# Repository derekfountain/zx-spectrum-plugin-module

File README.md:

# ZX Spectrum Plugin Module

This is small interposer board I created for the ZX Spectrum's edge connector.

## Improved edge connector

The Spectrum's edge connector can be rather tight, and repeated
insertion and removal of an interface you're prototyping can wear it
away. The copper pads are difficult to repair if they wear too thin
and stop working. Also, the edge connector sockets need cutting to
size and a locating pin inserting, which is all a bit fiddly and so
they are relatively expensive.

The interposer board converts the Spectrum's edge connector hardware
format to a much more standard row of 2.54" header pins. It looks like
this:

Front:

Back:

So you solder a Spectrum edge connector to the front:

and a couple of rows of standard header sockets to the back:

The board you're prototyping can then use standard header pins
in place the normal Spectrum edge connector socket:

This allows you to plug the prototype into the interposer, as opposed
to the Spectrum's edge connector:

So now the prototype can be put onto, and pulled off, the Spectrum
without wearing the edge connector, and each prototype iteration costs
you 2 rows of standard header pins instead of an edge connector
socket.

## Another use

A rather unintended alternative use for the board is to expose the
edge connector pins more easily. It's a lot easier to insert a wire
into a header socket and connect the other end to the oscilloscope
probe than it is to try to get the probe on a certain Z80 pin, for
example.

To this end I ended up making a "breakout" version as well, which also
exposes the edge connector's signals on connection points. I'm not
sure this version is useful, since I think the prototype board and the
back of the Spectrum will foul access to the extra test points. I
didn't pursue it, but it might be useful to someone.

### Construction

Construction is trivial, but try to use long strip of sockets cut
down, as opposed to what I did which was use a strip of 20 butted up
against a strip of 8. It turns out the sides of the strips are
slightly thicker plastic then that between the connection points, so
when you butt them up together you get a wider gap between the
individual points at the joint. It's very slight, just a fraction of a
millimetre, but it makes fitting the header pins into the sockets a
bit tighter than it needs to be.

### Licence

Released under the GPL, which might not mean much to a hardware
design. If you make any useful modifications to it, stick to the
spirit and release them. :)

[Derek Fountain](https://www.derekfountain.org/), September 2023

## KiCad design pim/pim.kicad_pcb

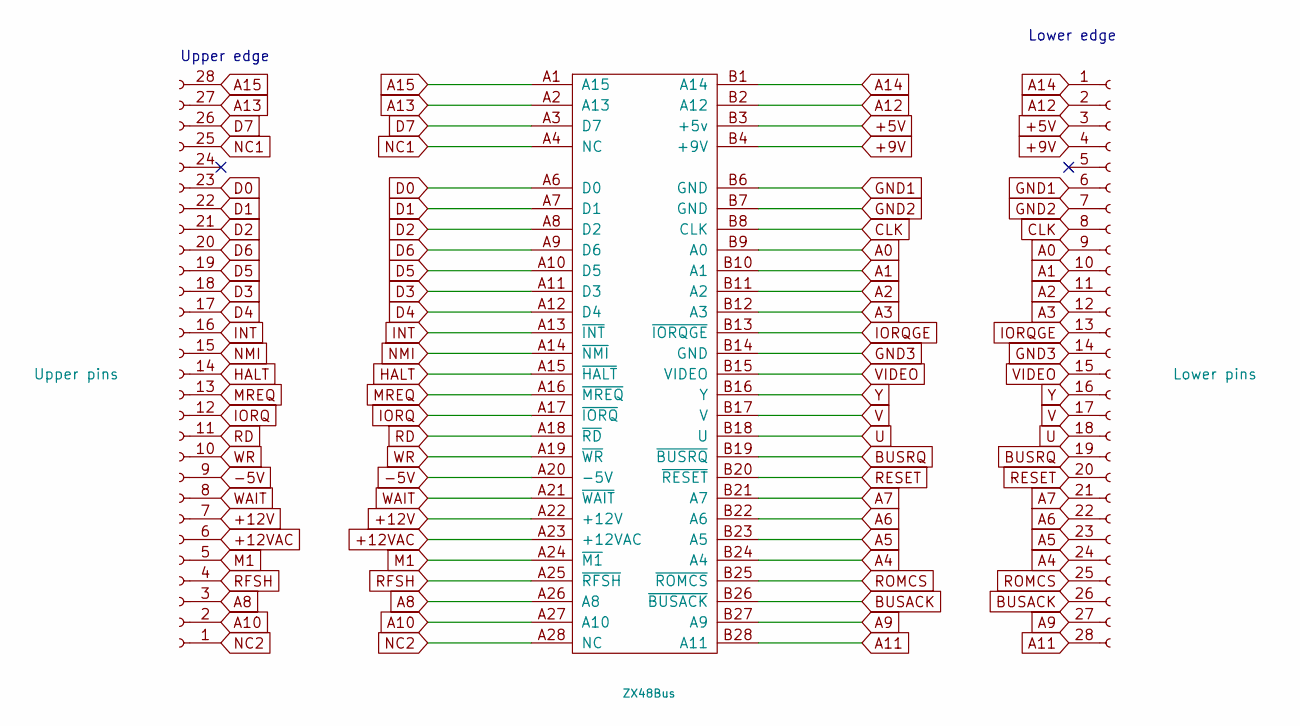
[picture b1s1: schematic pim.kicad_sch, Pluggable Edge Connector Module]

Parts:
J1: Upper pins; PinHeader_1x28_P2.54mm_Vertical
J2: Lower pins; PinHeader_1x28_P2.54mm_Vertical
Z1: ZX48Bus; ZX_Bus_Pin_Header

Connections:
+5V: J2.3, Z1.B3 (+5v)
+9V: J2.4, Z1.B4 (+9V)
+12V: J1.7, Z1.A22 (+12V)
+12VAC: J1.6, Z1.A23 (+12VAC)
-5V: J1.9, Z1.A20 (-5V)
A0: J2.9, Z1.B9 (A0)
A1: J2.10, Z1.B10 (A1)
A2: J2.11, Z1.B11 (A2)
A3: J2.12, Z1.B12 (A3)
A4: J2.24, Z1.B24 (A4)
A5: J2.23, Z1.B23 (A5)
A6: J2.22, Z1.B22 (A6)
A7: J2.21, Z1.B21 (A7)
A8: J1.3, Z1.A26 (A8)
A9: J2.27, Z1.B27 (A9)
A10: J1.2, Z1.A27 (A10)
A11: J2.28, Z1.B28 (A11)
A12: J2.2, Z1.B2 (A12)
A13: J1.27, Z1.A2 (A13)
A14: J2.1, Z1.B1 (A14)
A15: J1.28, Z1.A1 (A15)
BUSACK: J2.26, Z1.B26 (~BUSACK)
BUSRQ: J2.19, Z1.B19 (~BUSRQ)
CLK: J2.8, Z1.B8 (CLK)
D0: J1.23, Z1.A6 (D0)
D1: J1.22, Z1.A7 (D1)
D2: J1.21, Z1.A8 (D2)
D3: J1.18, Z1.A11 (D3)
D4: J1.17, Z1.A12 (D4)
D5: J1.19, Z1.A10 (D5)
D6: J1.20, Z1.A9 (D6)
D7: J1.26, Z1.A3 (D7)
GND1: J2.6, Z1.B6 (GND)
GND2: J2.7, Z1.B7 (GND)
GND3: J2.14, Z1.B14 (GND)
HALT: J1.14, Z1.A15 (~HALT)
INT: J1.16, Z1.A13 (~INT)
IORQ: J1.12, Z1.A17 (~IORQ)
IORQGE: J2.13, Z1.B13 (~IORQGE)
M1: J1.5, Z1.A24 (~M1)
MREQ: J1.13, Z1.A16 (~MREQ)
NC1: J1.25, Z1.A4 (NC)
NC2: J1.1, Z1.A28 (NC)
NMI: J1.15, Z1.A14 (~NMI)
RD: J1.11, Z1.A18 (~RD)
RESET: J2.20, Z1.B20 (~RESET)
RFSH: J1.4, Z1.A25 (~RFSH)
ROMCS: J2.25, Z1.B25 (~ROMCS)
U: J2.18, Z1.B18 (U)
V: J2.17, Z1.B17 (V)
VIDEO: J2.15, Z1.B15 (VIDEO)
WAIT: J1.8, Z1.A21 (~WAIT)
WR: J1.10, Z1.A19 (~WR)
Y: J2.16, Z1.B16 (Y)

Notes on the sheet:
Upper edge
Lower edge

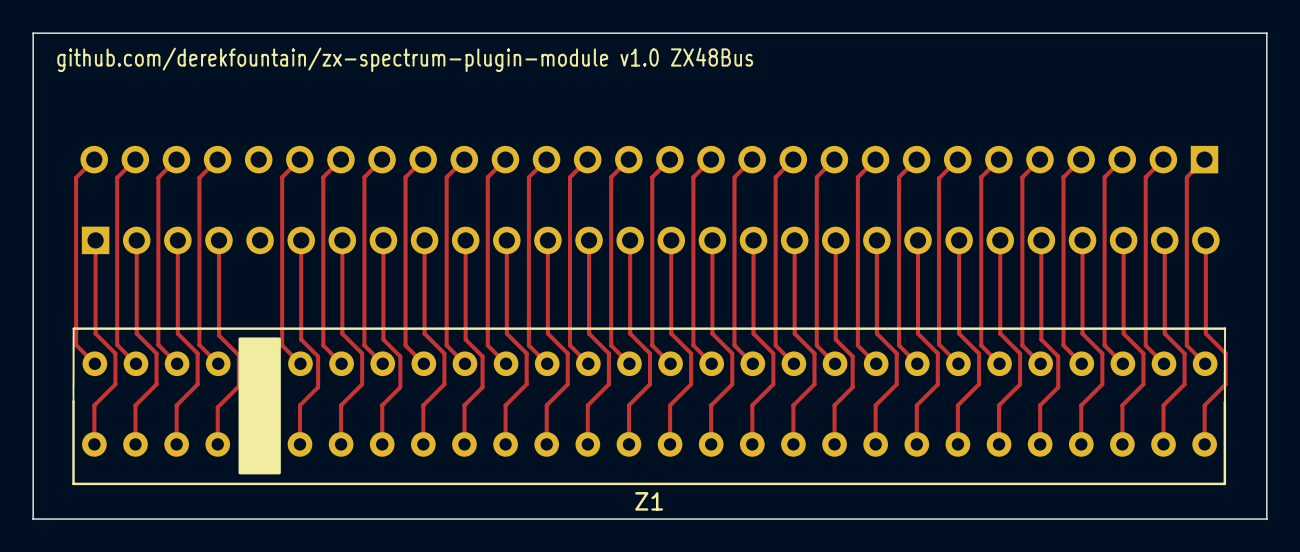
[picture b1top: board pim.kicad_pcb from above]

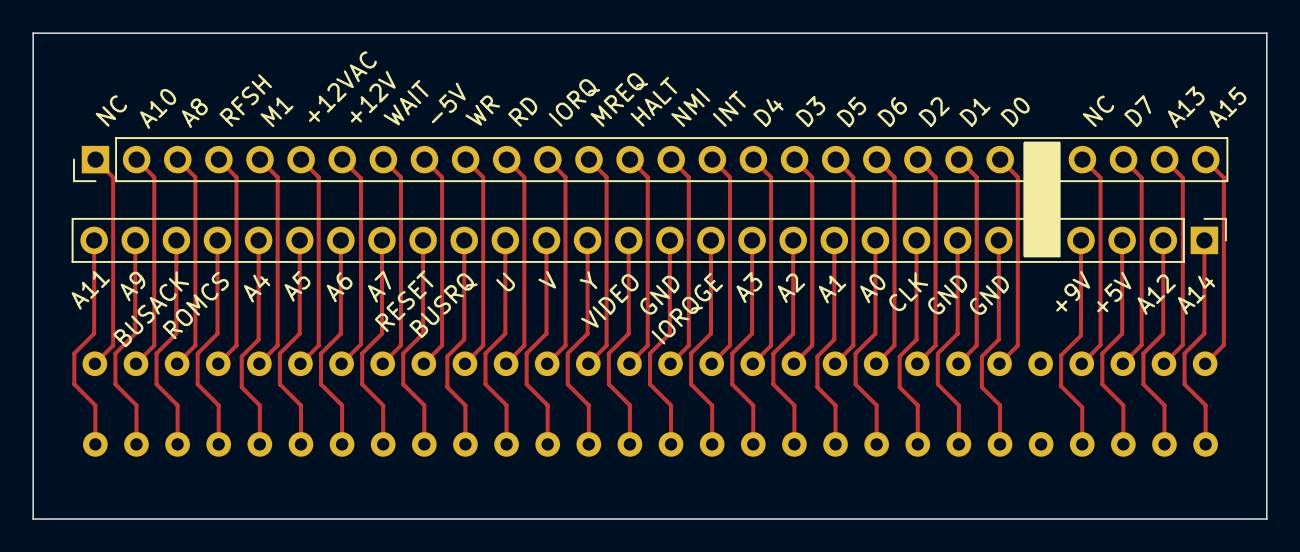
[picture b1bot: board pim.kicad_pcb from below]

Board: 2 copper layers, 76.2 x 30.0 mm, 3 parts (2 on the bottom side), 54 nets.

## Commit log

2023-02-13 initial design
2023-02-13 widen connector to match the ones i have
2023-02-13 ready for a v1.0 fab
2023-02-14 breakout idea separated, i'm not convinced it's useful
2023-02-14 start an example board, not sure what to do with it yet
2023-09-08 Add readme and some images of first constructed version
